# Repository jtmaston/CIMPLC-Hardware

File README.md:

<div style="text-align: justify">

# CIMPLC
The CIMPLC is a low-cost, open source high pin-count programmable logic controller, designed as a project while studying at the University of Politehnica, Bucharest. It is designed as a replacement for the aging hardware found inside the CIM ( Computer Integrated Manufacturing ) located in our faculty.

# The hardware
The CIMPLC is based, as much as possible, on readily-available parts. Since the hardware development time had to be reduced as much as possible, it was decided to simplify the control hardware, by using an ESP32 Devkit v4 at the core. Beyond that, the goal was to employ as many interfaces as possible compatible to the CIM.

## Features

### Interfaces
- RS232
- RS485
- ~~CAN~~ (See limitations)
- WiFi / Bluetooth

### Input / Output
- 12 Inputs
- 32 Outputs

### Program memory
- 125KB of EEPROM for user program storage
- 4MB of external SRAM, used for instruction caching

### Programmability
- Over the air (OTA) firmware updates
- Built-in optimizing compiler to translate IEC 61131-3 instructions to bytecode which can be loaded faster from EEPROM.
## Limitations

- Due to the fast development cycle and my inexperience with electronics, the outputs are only able to source current, not sink. The implementation, using solid-state relays, allow to source +12v when the pin is driven high, but otherwise leaves the pin floating.

- Similarly, due to my inexperience, I avoided implementing onboard power management, relying on an external +12v power supply, able to drive the pin outputs, as well as a +5v rail to power the control side. There will probably be more things , but this is all I've discovered up at this point.

- An oversight has been the fact that strapping pins 0 and 2 have been used, which control going into the bootloader. As such, all reboots would necessitate the CANH line being high.
As such, it has been removed and functionality abandoned.

## License

This project is licensed under the [CERN OHL v2 Weakly Reciprocal](https://choosealicense.com/licenses/cern-ohl-w-2.0/).

</div>

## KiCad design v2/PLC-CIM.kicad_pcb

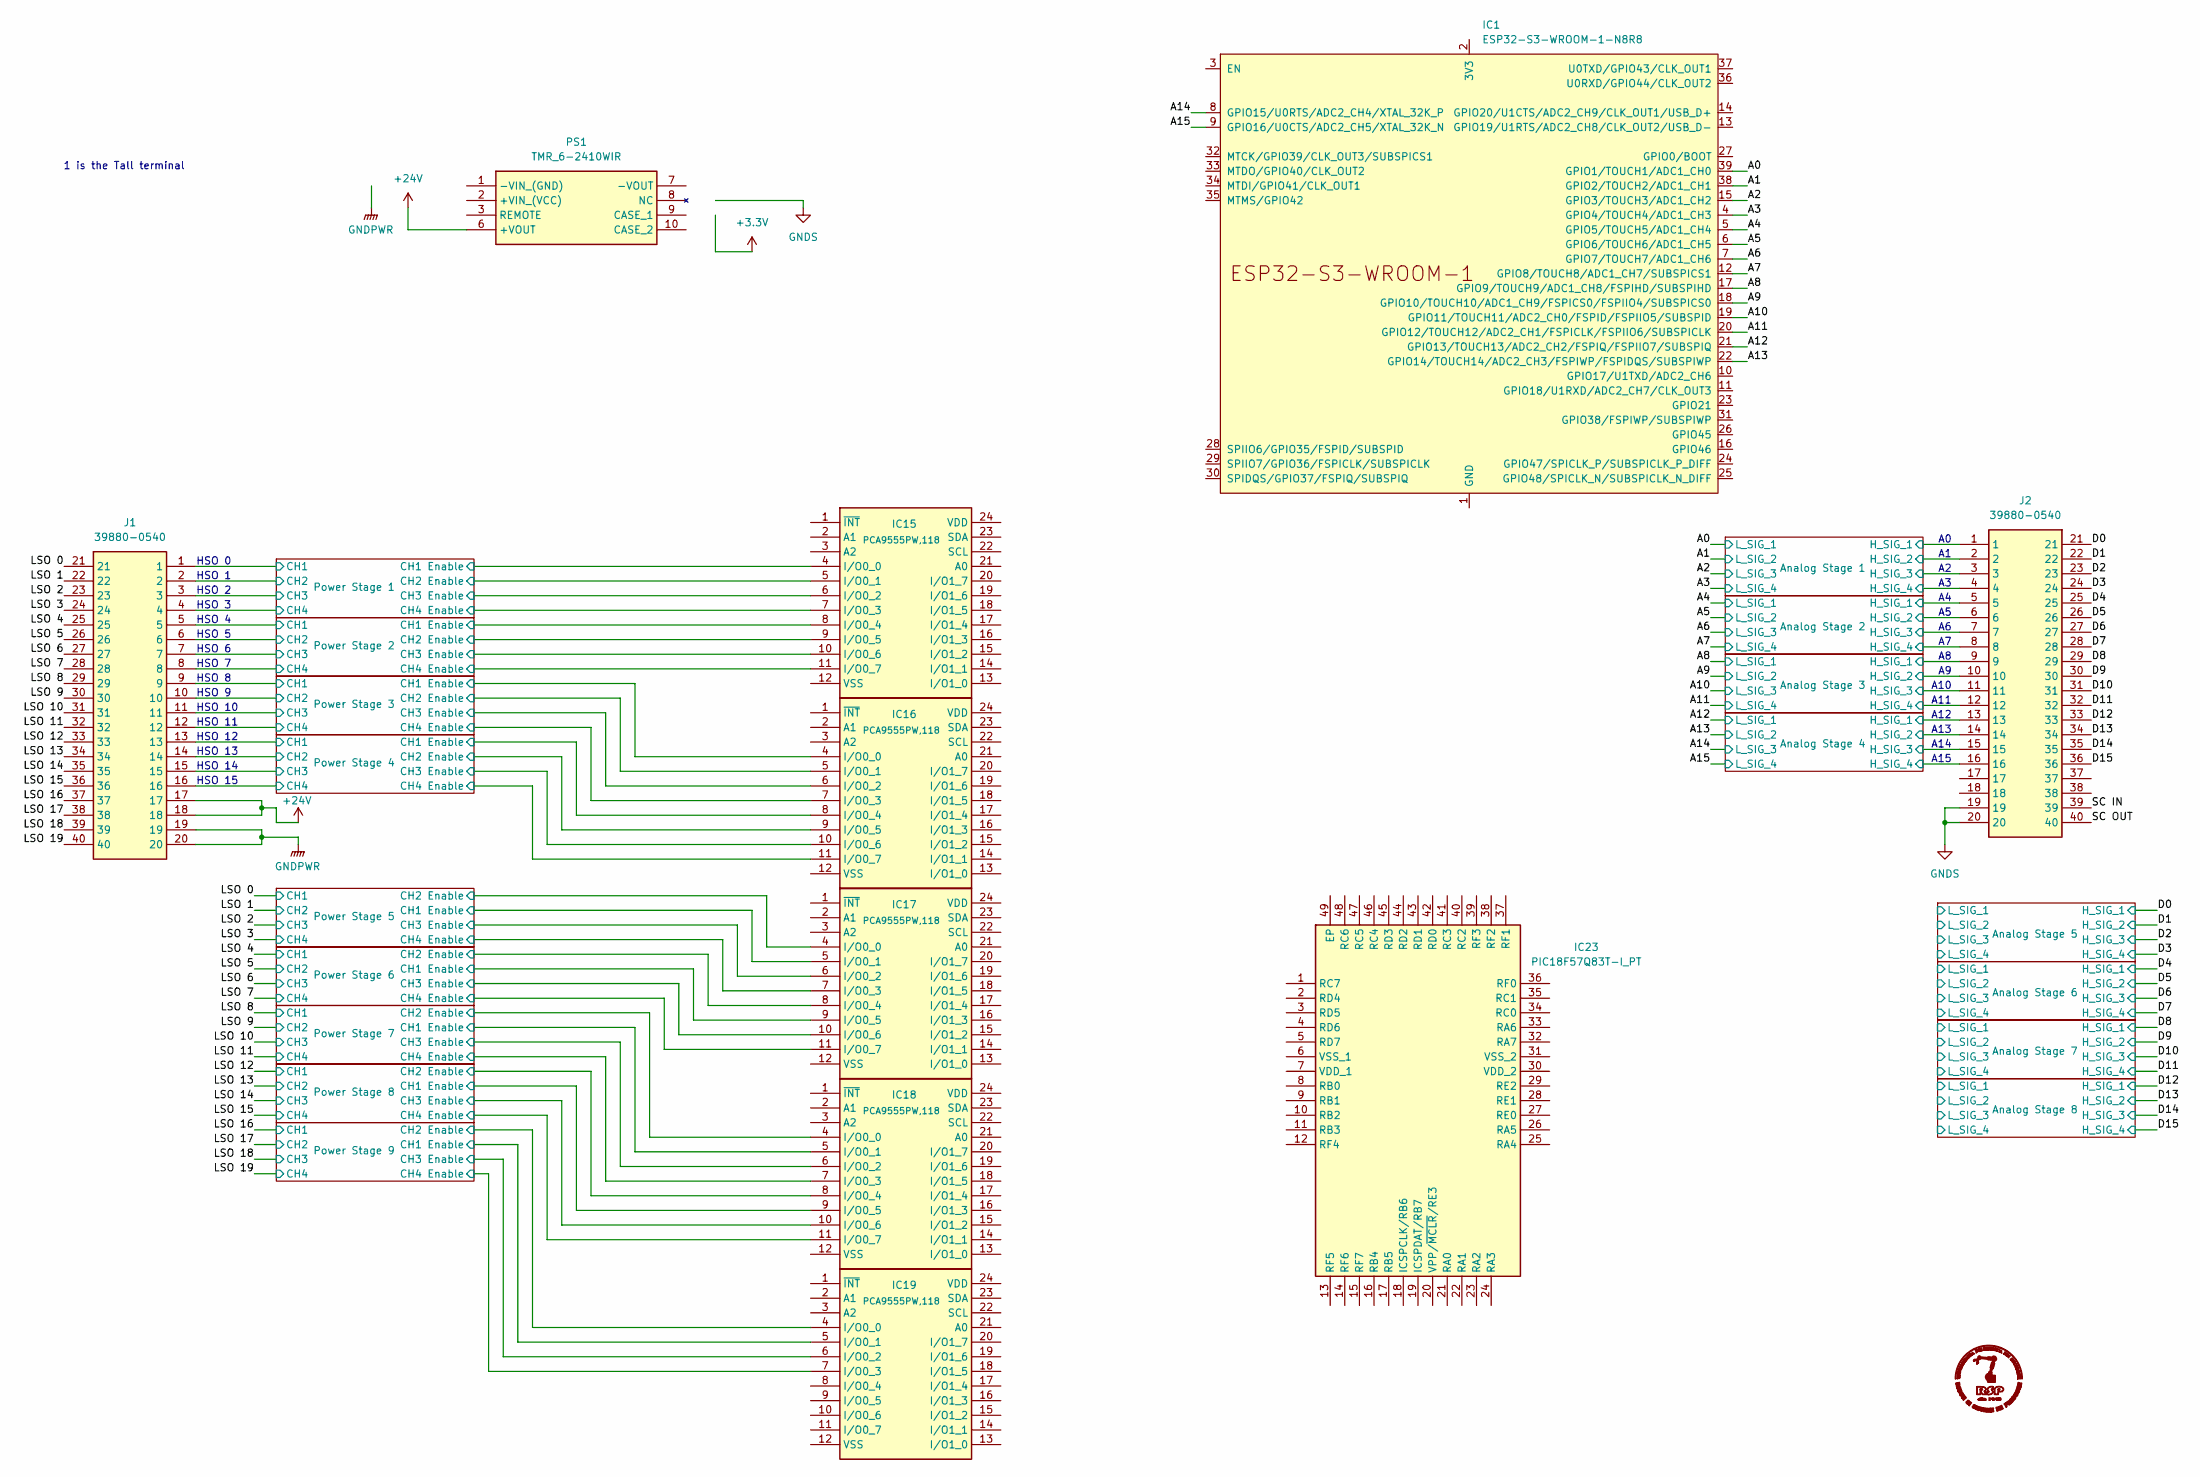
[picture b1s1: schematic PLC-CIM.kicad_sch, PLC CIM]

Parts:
IC1: ESP32-S3-WROOM-1-N8R8; ESP32S3WROOM1N8R8; Mouser Part Number 356-EP32S3WROOM1N8R8
IC15, IC16, IC17, IC18, IC19: PCA9555PW,118; SOP65P640X110-24N; Mouser Part Number 771-PCA9555PW-T
IC23: PIC18F57Q83T-I_PT; QFP50P900X900X120-49N; Mouser Part Number N/A
J1, J2: 39880-0540; 398800540; Mouser Part Number 538-39880-0540
PS1: TMR_6-2410WIR; TMR62410WIR; Mouser Part Number 495-TMR6-2410WIR

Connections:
+24V: J1.17, J1.18, PS1.6 (+VOUT); also elsewhere on the board
/A0: IC1.39 (GPIO1/TOUCH1/ADC1_CH0); also elsewhere on the board
/A1: IC1.38 (GPIO2/TOUCH2/ADC1_CH1); also elsewhere on the board
/A2: IC1.15 (GPIO3/TOUCH3/ADC1_CH2); also elsewhere on the board
/A3: IC1.4 (GPIO4/TOUCH4/ADC1_CH3); also elsewhere on the board
/A4: IC1.5 (GPIO5/TOUCH5/ADC1_CH4); also elsewhere on the board
/A5: IC1.6 (GPIO6/TOUCH6/ADC1_CH5); also elsewhere on the board
/A6: IC1.7 (GPIO7/TOUCH7/ADC1_CH6); also elsewhere on the board
/A7: IC1.12 (GPIO8/TOUCH8/ADC1_CH7/SUBSPICS1); also elsewhere on the board
/A8: IC1.17 (GPIO9/TOUCH9/ADC1_CH8/FSPIHD/SUBSPIHD); also elsewhere on the board
/A9: IC1.18 (GPIO10/TOUCH10/ADC1_CH9/FSPICS0/FSPIIO4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); also elsewhere on the board
/A10: IC1.19 (GPIO11/TOUCH11/ADC2_CH0/FSPID/FSPIIO5/S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); also elsewhere on the board
/A11: IC1.20 (GPIO12/TOUCH12/ADC2_CH1/FSPICLK/FSPIIO6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); also elsewhere on the board
/A12: IC1.21 (GPIO13/TOUCH13/ADC2_CH2/FSPIQ/FSPIIO7/S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); also elsewhere on the board
/A13: IC1.22 (GPIO14/TOUCH14/ADC2_CH3/FSPIWP/FSPIDQS/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); also elsewhere on the board
/A14: IC1.8 (GPIO15/U0RTS/ADC2_CH4/XTAL_32K_P); also elsewhere on the board
/A15: IC1.9 (GPIO16/U0CTS/ADC2_CH5/XTAL_32K_N); also elsewhere on the board
/Analog Stage 1/H_SIG_1: J2.1; also elsewhere on the board
/Analog Stage 1/H_SIG_2: J2.2; also elsewhere on the board
/Analog Stage 1/H_SIG_3: J2.3; also elsewhere on the board
/Analog Stage 1/H_SIG_4: J2.4; also elsewhere on the board
/Analog Stage 2/H_SIG_1: J2.5; also elsewhere on the board
/Analog Stage 2/H_SIG_2: J2.6; also elsewhere on the board
/Analog Stage 2/H_SIG_3: J2.7; also elsewhere on the board
/Analog Stage 2/H_SIG_4: J2.8; also elsewhere on the board
/Analog Stage 3/H_SIG_1: J2.9; also elsewhere on the board
/Analog Stage 3/H_SIG_2: J2.10; also elsewhere on the board
/Analog Stage 3/H_SIG_3: J2.11; also elsewhere on the board
/Analog Stage 3/H_SIG_4: J2.12; also elsewhere on the board
/Analog Stage 4/H_SIG_1: J2.13; also elsewhere on the board
/Analog Stage 4/H_SIG_2: J2.14; also elsewhere on the board
/Analog Stage 4/H_SIG_3: J2.15; also elsewhere on the board
/Analog Stage 4/H_SIG_4: J2.16; also elsewhere on the board
/D0: J2.21; also elsewhere on the board
/D1: J2.22; also elsewhere on the board
/D2: J2.23; also elsewhere on the board
/D3: J2.24; also elsewhere on the board
/D4: J2.25; also elsewhere on the board
/D5: J2.26; also elsewhere on the board
/D6: J2.27; also elsewhere on the board
/D7: J2.28; also elsewhere on the board
/D8: J2.29; also elsewhere on the board
/D9: J2.30; also elsewhere on the board
/D10: J2.31; also elsewhere on the board
/D11: J2.32; also elsewhere on the board
/D12: J2.33; also elsewhere on the board
/D13: J2.34; also elsewhere on the board
/D14: J2.35; also elsewhere on the board
/D15: J2.36; also elsewhere on the board
/LSO 0: J1.21; also elsewhere on the board
/LSO 1: J1.22; also elsewhere on the board
/LSO 2: J1.23; also elsewhere on the board
/LSO 3: J1.24; also elsewhere on the board
/LSO 4: J1.25; also elsewhere on the board
/LSO 5: J1.26; also elsewhere on the board
/LSO 6: J1.27; also elsewhere on the board
/LSO 7: J1.28; also elsewhere on the board
/LSO 8: J1.29; also elsewhere on the board
/LSO 9: J1.30; also elsewhere on the board
/LSO 10: J1.31; also elsewhere on the board
/LSO 11: J1.32; also elsewhere on the board
/LSO 12: J1.33; also elsewhere on the board
/LSO 13: J1.34; also elsewhere on the board
/LSO 14: J1.35; also elsewhere on the board
/LSO 15: J1.36; also elsewhere on the board
/LSO 16: J1.37; also elsewhere on the board
/LSO 17: J1.38; also elsewhere on the board
/LSO 18: J1.39; also elsewhere on the board
/LSO 19: J1.40; also elsewhere on the board
/Power Stage 1/CH1: J1.1; also elsewhere on the board
/Power Stage 1/CH1 Enable: IC15.4 (I/O0_0); also elsewhere on the board
/Power Stage 1/CH2: J1.2; also elsewhere on the board
/Power Stage 1/CH2 Enable: IC15.5 (I/O0_1); also elsewhere on the board
/Power Stage 1/CH3: J1.3; also elsewhere on the board
/Power Stage 1/CH3 Enable: IC15.6 (I/O0_2); also elsewhere on the board
/Power Stage 1/CH4: J1.4; also elsewhere on the board
/Power Stage 1/CH4 Enable: IC15.7 (I/O0_3); also elsewhere on the board
/Power Stage 2/CH1: J1.5; also elsewhere on the board
/Power Stage 2/CH1 Enable: IC15.8 (I/O0_4); also elsewhere on the board
/Power Stage 2/CH2: J1.6; also elsewhere on the board
/Power Stage 2/CH2 Enable: IC15.9 (I/O0_5); also elsewhere on the board
/Power Stage 2/CH3: J1.7; also elsewhere on the board
/Power Stage 2/CH3 Enable: IC15.10 (I/O0_6); also elsewhere on the board
/Power Stage 2/CH4: J1.8; also elsewhere on the board
/Power Stage 2/CH4 Enable: IC15.11 (I/O0_7); also elsewhere on the board
/Power Stage 3/CH1: J1.9; also elsewhere on the board
/Power Stage 3/CH1 Enable: IC16.4 (I/O0_0); also elsewhere on the board
/Power Stage 3/CH2: J1.10; also elsewhere on the board
/Power Stage 3/CH2 Enable: IC16.5 (I/O0_1); also elsewhere on the board
/Power Stage 3/CH3: J1.11; also elsewhere on the board
/Power Stage 3/CH3 Enable: IC16.6 (I/O0_2); also elsewhere on the board
/Power Stage 3/CH4: J1.12; also elsewhere on the board
/Power Stage 3/CH4 Enable: IC16.7 (I/O0_3); also elsewhere on the board
/Power Stage 4/CH1: J1.13; also elsewhere on the board
/Power Stage 4/CH1 Enable: IC16.8 (I/O0_4); also elsewhere on the board
/Power Stage 4/CH2: J1.14; also elsewhere on the board
/Power Stage 4/CH2 Enable: IC16.9 (I/O0_5); also elsewhere on the board
/Power Stage 4/CH3: J1.15; also elsewhere on the board
/Power Stage 4/CH3 Enable: IC16.10 (I/O0_6); also elsewhere on the board
/Power Stage 4/CH4: J1.16; also elsewhere on the board
/Power Stage 4/CH4 Enable: IC16.11 (I/O0_7); also elsewhere on the board
/Power Stage 5/CH1 Enable: IC17.5 (I/O0_1); also elsewhere on the board
/Power Stage 5/CH2 Enable: IC17.4 (I/O0_0); also elsewhere on the board
/Power Stage 5/CH3 Enable: IC17.6 (I/O0_2); also elsewhere on the board
/Power Stage 5/CH4 Enable: IC17.7 (I/O0_3); also elsewhere on the board
/Power Stage 6/CH1 Enable: IC17.9 (I/O0_5); also elsewhere on the board
/Power Stage 6/CH2 Enable: IC17.8 (I/O0_4); also elsewhere on the board
/Power Stage 6/CH3 Enable: IC17.10 (I/O0_6); also elsewhere on the board
/Power Stage 6/CH4 Enable: IC17.11 (I/O0_7); also elsewhere on the board
/Power Stage 7/CH1 Enable: IC18.5 (I/O0_1); also elsewhere on the board
/Power Stage 7/CH2 Enable: IC18.4 (I/O0_0); also elsewhere on the board
/Power Stage 7/CH3 Enable: IC18.6 (I/O0_2); also elsewhere on the board
/Power Stage 7/CH4 Enable: IC18.7 (I/O0_3); also elsewhere on the board
/Power Stage 8/CH1 Enable: IC18.9 (I/O0_5); also elsewhere on the board
/Power Stage 8/CH2 Enable: IC18.8 (I/O0_4); also elsewhere on the board
/Power Stage 8/CH3 Enable: IC18.10 (I/O0_6); also elsewhere on the board
/Power Stage 8/CH4 Enable: IC18.11 (I/O0_7); also elsewhere on the board
/Power Stage 9/CH1 Enable: IC19.5 (I/O0_1); also elsewhere on the board
/Power Stage 9/CH2 Enable: IC19.4 (I/O0_0); also elsewhere on the board
/Power Stage 9/CH3 Enable: IC19.6 (I/O0_2); also elsewhere on the board
/Power Stage 9/CH4 Enable: IC19.7 (I/O0_3); also elsewhere on the board
/SC IN: J2.39
/SC OUT: J2.40
GNDPWR: J1.19, J1.20; also elsewhere on the board
GNDS: J2.19, J2.20; also elsewhere on the board
unnamed: IC1.1 (GND), IC1.40 (GND), IC1.41 (GND)

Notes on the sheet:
HSO 4
HSO 11
HSO 0
A12
HSO 10
HSO 15
HSO 12
A14
1 is the Tall terminal
HSO 13
HSO 5
HSO 14
HSO 3
A13
HSO 9
HSO 2
HSO 1
HSO 8
HSO 6
A10
HSO 7
A11
A15

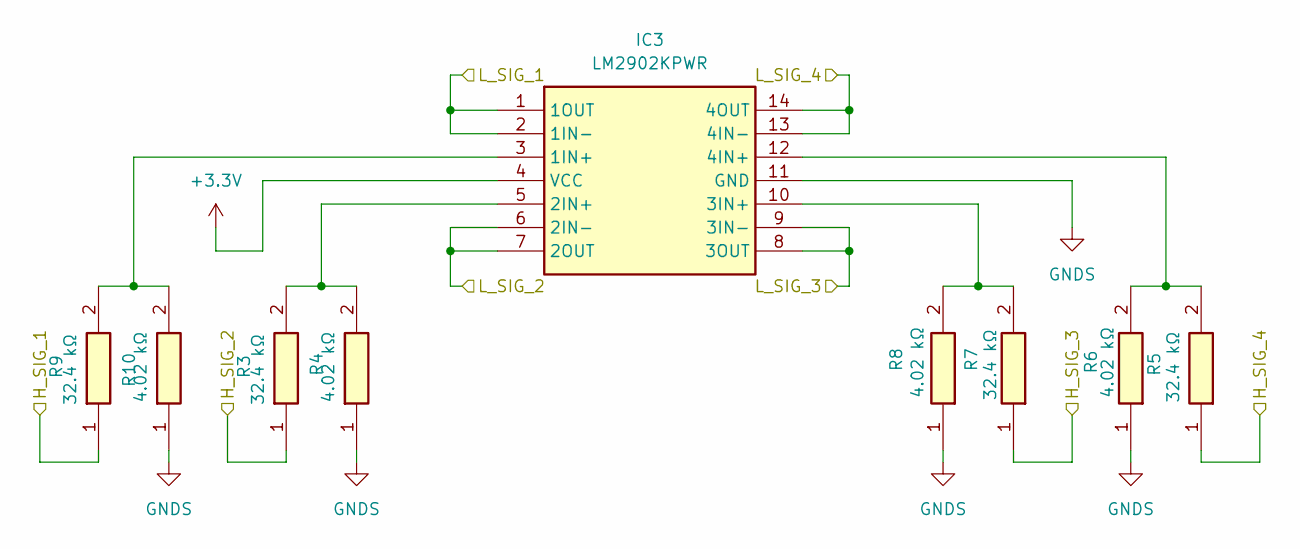
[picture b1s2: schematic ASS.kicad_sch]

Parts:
IC3: LM2902KPWR; SOP65P640X120-14N; Mouser Part Number 595-LM2902KPWR
R3, R5, R7, R9: 32.4 kΩ; RESC1609X55N; Mouser Part Number 667-ERJ-P03F3242V
R4, R6, R8, R10: 4.02 kΩ; RESC1609X55N; Mouser Part Number 71-CRCW12064K02FKEAH

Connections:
+3.3V: IC3.4 (VCC); also elsewhere on the board
/A4: IC3.1 (1OUT), IC3.2 (1IN-); also elsewhere on the board
/A5: IC3.6 (2IN-), IC3.7 (2OUT); also elsewhere on the board
/A6: IC3.8 (3OUT), IC3.9 (3IN-); also elsewhere on the board
/A7: IC3.13 (4IN-), IC3.14 (4OUT); also elsewhere on the board
/Analog Stage 1/H_SIG_2: R3.1; also elsewhere on the board
/Analog Stage 1/H_SIG_3: R7.1; also elsewhere on the board
/Analog Stage 1/H_SIG_4: R5.1; also elsewhere on the board
/Analog Stage 2/H_SIG_1: R9.1; also elsewhere on the board
GNDS: IC3.11 (GND), R4.1, R6.1, R8.1, R10.1; also elsewhere on the board
unnamed: IC3.3 (1IN+), R9.2, R10.2

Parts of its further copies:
IC2, IC4, IC5, IC20, IC21, IC22, IC24: LM2902KPWR; SOP65P640X120-14N; Mouser Part Number 595-LM2902KPWR
R1, R11, R14, R16, R17, R19, R22, R24, R25, R27, R30, R32, R33, R35, R38, R40, R41, R44, R46, R47, R49, R52, R54, R55, R57, R60, R62, R63: 32.4 kΩ; RESC1609X55N; Mouser Part Number 667-ERJ-P03F3242V
R2, R12, R13, R15, R18, R20, R21, R23, R26, R28, R29, R31, R34, R36, R37, R39, R42, R43, R45, R48, R50, R51, R53, R56, R58, R59, R61, R64: 4.02 kΩ; RESC1609X55N; Mouser Part Number 71-CRCW12064K02FKEAH

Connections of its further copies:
+3.3V: IC2.4 (VCC), IC4.4 (VCC), IC5.4 (VCC), IC20.4 (VCC), IC21.4 (VCC), IC22.4 (VCC), IC24.4 (VCC); also elsewhere on the board
/A0: IC24.1 (1OUT), IC24.2 (1IN-); also elsewhere on the board
/A1: IC24.6 (2IN-), IC24.7 (2OUT); also elsewhere on the board
/A2: IC24.8 (3OUT), IC24.9 (3IN-); also elsewhere on the board
/A3: IC24.13 (4IN-), IC24.14 (4OUT); also elsewhere on the board
/A8: IC4.1 (1OUT), IC4.2 (1IN-); also elsewhere on the board
/A9: IC4.6 (2IN-), IC4.7 (2OUT); also elsewhere on the board
/A10: IC4.8 (3OUT), IC4.9 (3IN-); also elsewhere on the board
/A11: IC4.13 (4IN-), IC4.14 (4OUT); also elsewhere on the board
/A12: IC5.1 (1OUT), IC5.2 (1IN-); also elsewhere on the board
/A13: IC5.6 (2IN-), IC5.7 (2OUT); also elsewhere on the board
/A14: IC5.8 (3OUT), IC5.9 (3IN-); also elsewhere on the board
/A15: IC5.13 (4IN-), IC5.14 (4OUT); also elsewhere on the board
/Analog Stage 1/H_SIG_1: R25.1; also elsewhere on the board
/Analog Stage 2/H_SIG_2: R11.1; also elsewhere on the board
/Analog Stage 2/H_SIG_3: R14.1; also elsewhere on the board
/Analog Stage 2/H_SIG_4: R16.1; also elsewhere on the board
/Analog Stage 3/H_SIG_1: R17.1; also elsewhere on the board
/Analog Stage 3/H_SIG_2: R19.1; also elsewhere on the board
/Analog Stage 3/H_SIG_3: R22.1; also elsewhere on the board
/Analog Stage 3/H_SIG_4: R24.1; also elsewhere on the board
/Analog Stage 4/H_SIG_1: R63.1; also elsewhere on the board
/Analog Stage 4/H_SIG_2: R27.1; also elsewhere on the board
/Analog Stage 4/H_SIG_3: R30.1; also elsewhere on the board
/Analog Stage 4/H_SIG_4: R32.1; also elsewhere on the board
/Analog Stage 5/L_SIG_1: IC20.1 (1OUT), IC20.2 (1IN-)
/Analog Stage 5/L_SIG_2: IC20.6 (2IN-), IC20.7 (2OUT)
/Analog Stage 5/L_SIG_3: IC20.8 (3OUT), IC20.9 (3IN-)
/Analog Stage 5/L_SIG_4: IC20.13 (4IN-), IC20.14 (4OUT)
/Analog Stage 6/L_SIG_1: IC2.1 (1OUT), IC2.2 (1IN-)
/Analog Stage 6/L_SIG_2: IC2.6 (2IN-), IC2.7 (2OUT)
/Analog Stage 6/L_SIG_3: IC2.8 (3OUT), IC2.9 (3IN-)
/Analog Stage 6/L_SIG_4: IC2.13 (4IN-), IC2.14 (4OUT)
/Analog Stage 7/L_SIG_1: IC21.1 (1OUT), IC21.2 (1IN-)
/Analog Stage 7/L_SIG_2: IC21.6 (2IN-), IC21.7 (2OUT)
/Analog Stage 7/L_SIG_3: IC21.8 (3OUT), IC21.9 (3IN-)
/Analog Stage 7/L_SIG_4: IC21.13 (4IN-), IC21.14 (4OUT)
/Analog Stage 8/L_SIG_1: IC22.1 (1OUT), IC22.2 (1IN-)
/Analog Stage 8/L_SIG_2: IC22.6 (2IN-), IC22.7 (2OUT)
/Analog Stage 8/L_SIG_3: IC22.8 (3OUT), IC22.9 (3IN-)
/Analog Stage 8/L_SIG_4: IC22.13 (4IN-), IC22.14 (4OUT)
/D0: R33.1; also elsewhere on the board
/D1: R35.1; also elsewhere on the board
/D2: R38.1; also elsewhere on the board
/D3: R40.1; also elsewhere on the board
/D4: R1.1; also elsewhere on the board
/D5: R41.1; also elsewhere on the board
/D6: R44.1; also elsewhere on the board
/D7: R46.1; also elsewhere on the board
/D8: R47.1; also elsewhere on the board
/D9: R49.1; also elsewhere on the board
/D10: R52.1; also elsewhere on the board
/D11: R54.1; also elsewhere on the board
/D12: R55.1; also elsewhere on the board
/D13: R57.1; also elsewhere on the board
/D14: R60.1; also elsewhere on the board
/D15: R62.1; also elsewhere on the board
GNDS: IC2.11 (GND), IC4.11 (GND), IC5.11 (GND), IC20.11 (GND), IC21.11 (GND), IC22.11 (GND), IC24.11 (GND), R2.1, R12.1, R13.1, R15.1, R18.1, R20.1, R21.1, R23.1, R26.1, R28.1, R29.1, R31.1, R34.1, R36.1, R37.1, R39.1, R42.1, R43.1, R45.1, R48.1, R50.1, R51.1, R53.1, R56.1, R58.1, R59.1, R61.1, R64.1; also elsewhere on the board
unnamed: IC2.3 (1IN+), R1.2, R2.2
unnamed: IC2.5 (2IN+), R41.2, R42.2
unnamed: IC2.10 (3IN+), R43.2, R44.2
unnamed: IC2.12 (4IN+), R45.2, R46.2
unnamed: IC4.3 (1IN+), R17.2, R18.2
unnamed: IC4.5 (2IN+), R19.2, R20.2
unnamed: IC4.10 (3IN+), R21.2, R22.2
unnamed: IC4.12 (4IN+), R23.2, R24.2
unnamed: IC5.3 (1IN+), R63.2, R64.2
unnamed: IC5.5 (2IN+), R27.2, R28.2
unnamed: IC5.10 (3IN+), R29.2, R30.2
unnamed: IC5.12 (4IN+), R31.2, R32.2
unnamed: IC20.3 (1IN+), R33.2, R34.2
unnamed: IC20.5 (2IN+), R35.2, R36.2
unnamed: IC20.10 (3IN+), R37.2, R38.2
unnamed: IC20.12 (4IN+), R39.2, R40.2
unnamed: IC21.3 (1IN+), R47.2, R48.2
unnamed: IC21.5 (2IN+), R49.2, R50.2
unnamed: IC21.10 (3IN+), R51.2, R52.2
unnamed: IC21.12 (4IN+), R53.2, R54.2
unnamed: IC22.3 (1IN+), R55.2, R56.2
unnamed: IC22.5 (2IN+), R57.2, R58.2
unnamed: IC22.10 (3IN+), R59.2, R60.2
unnamed: IC22.12 (4IN+), R61.2, R62.2
unnamed: IC24.3 (1IN+), R25.2, R26.2

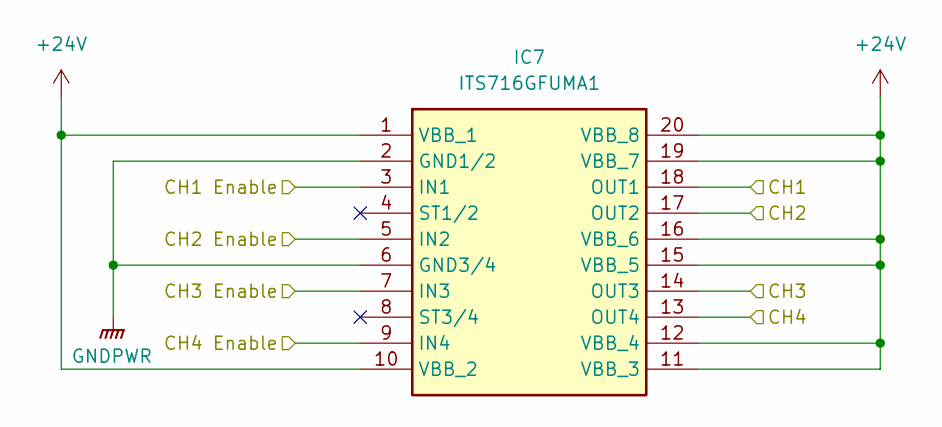
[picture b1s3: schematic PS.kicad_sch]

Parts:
IC7: ITS716GFUMA1; SOIC127P1030X265-20N; Mouser Part Number 726-ITS716GFUMA1

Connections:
+24V: IC7.1 (VBB_1), IC7.10 (VBB_2), IC7.11 (VBB_3), IC7.12 (VBB_4), IC7.15 (VBB_5), IC7.16 (VBB_6), IC7.19 (VBB_7), IC7.20 (VBB_8); also elsewhere on the board
/Power Stage 2/CH1: IC7.18 (OUT1); also elsewhere on the board
/Power Stage 2/CH1 Enable: IC7.3 (IN1); also elsewhere on the board
/Power Stage 2/CH2: IC7.17 (OUT2); also elsewhere on the board
/Power Stage 2/CH2 Enable: IC7.5 (IN2); also elsewhere on the board
/Power Stage 2/CH3: IC7.14 (OUT3); also elsewhere on the board
/Power Stage 2/CH3 Enable: IC7.7 (IN3); also elsewhere on the board
/Power Stage 2/CH4: IC7.13 (OUT4); also elsewhere on the board
/Power Stage 2/CH4 Enable: IC7.9 (IN4); also elsewhere on the board
GNDPWR: IC7.2 (GND1/2), IC7.6 (GND3/4); also elsewhere on the board

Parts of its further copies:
IC6, IC8, IC9, IC10, IC11, IC12, IC13, IC14: ITS716GFUMA1; SOIC127P1030X265-20N; Mouser Part Number 726-ITS716GFUMA1

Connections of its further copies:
+24V: IC6.1 (VBB_1), IC6.10 (VBB_2), IC6.11 (VBB_3), IC6.12 (VBB_4), IC6.15 (VBB_5), IC6.16 (VBB_6), IC6.19 (VBB_7), IC6.20 (VBB_8), IC8.1 (VBB_1), IC8.10 (VBB_2), IC8.11 (VBB_3), IC8.12 (VBB_4), IC8.15 (VBB_5), IC8.16 (VBB_6), IC8.19 (VBB_7), IC8.20 (VBB_8), IC9.1 (VBB_1), IC9.10 (VBB_2), IC9.11 (VBB_3), IC9.12 (VBB_4), IC9.15 (VBB_5), IC9.16 (VBB_6), IC9.19 (VBB_7), IC9.20 (VBB_8), IC10.1 (VBB_1), IC10.10 (VBB_2), IC10.11 (VBB_3), IC10.12 (VBB_4), IC10.15 (VBB_5), IC10.16 (VBB_6), IC10.19 (VBB_7), IC10.20 (VBB_8), IC11.1 (VBB_1), IC11.10 (VBB_2), IC11.11 (VBB_3), IC11.12 (VBB_4), IC11.15 (VBB_5), IC11.16 (VBB_6), IC11.19 (VBB_7), IC11.20 (VBB_8), IC12.1 (VBB_1), IC12.10 (VBB_2), IC12.11 (VBB_3), IC12.12 (VBB_4), IC12.15 (VBB_5), IC12.16 (VBB_6), IC12.19 (VBB_7), IC12.20 (VBB_8), IC13.1 (VBB_1), IC13.10 (VBB_2), IC13.11 (VBB_3), IC13.12 (VBB_4), IC13.15 (VBB_5), IC13.16 (VBB_6), IC13.19 (VBB_7), IC13.20 (VBB_8), IC14.1 (VBB_1), IC14.10 (VBB_2), IC14.11 (VBB_3), IC14.12 (VBB_4), IC14.15 (VBB_5), IC14.16 (VBB_6), IC14.19 (VBB_7), IC14.20 (VBB_8); also elsewhere on the board
/LSO 0: IC10.18 (OUT1); also elsewhere on the board
/LSO 1: IC10.17 (OUT2); also elsewhere on the board
/LSO 2: IC10.14 (OUT3); also elsewhere on the board
/LSO 3: IC10.13 (OUT4); also elsewhere on the board
/LSO 4: IC11.18 (OUT1); also elsewhere on the board
/LSO 5: IC11.17 (OUT2); also elsewhere on the board
/LSO 6: IC11.14 (OUT3); also elsewhere on the board
/LSO 7: IC11.13 (OUT4); also elsewhere on the board
/LSO 8: IC12.18 (OUT1); also elsewhere on the board
/LSO 9: IC12.17 (OUT2); also elsewhere on the board
/LSO 10: IC12.14 (OUT3); also elsewhere on the board
/LSO 11: IC12.13 (OUT4); also elsewhere on the board
/LSO 12: IC13.18 (OUT1); also elsewhere on the board
/LSO 13: IC13.17 (OUT2); also elsewhere on the board
/LSO 14: IC13.14 (OUT3); also elsewhere on the board
/LSO 15: IC13.13 (OUT4); also elsewhere on the board
/LSO 16: IC14.18 (OUT1); also elsewhere on the board
/LSO 17: IC14.17 (OUT2); also elsewhere on the board
/LSO 18: IC14.14 (OUT3); also elsewhere on the board
/LSO 19: IC14.13 (OUT4); also elsewhere on the board
/Power Stage 1/CH1: IC6.18 (OUT1); also elsewhere on the board
/Power Stage 1/CH1 Enable: IC6.3 (IN1); also elsewhere on the board
/Power Stage 1/CH2: IC6.17 (OUT2); also elsewhere on the board
/Power Stage 1/CH2 Enable: IC6.5 (IN2); also elsewhere on the board
/Power Stage 1/CH3: IC6.14 (OUT3); also elsewhere on the board
/Power Stage 1/CH3 Enable: IC6.7 (IN3); also elsewhere on the board
/Power Stage 1/CH4: IC6.13 (OUT4); also elsewhere on the board
/Power Stage 1/CH4 Enable: IC6.9 (IN4); also elsewhere on the board
/Power Stage 3/CH1: IC8.18 (OUT1); also elsewhere on the board
/Power Stage 3/CH1 Enable: IC8.3 (IN1); also elsewhere on the board
/Power Stage 3/CH2: IC8.17 (OUT2); also elsewhere on the board
/Power Stage 3/CH2 Enable: IC8.5 (IN2); also elsewhere on the board
/Power Stage 3/CH3: IC8.14 (OUT3); also elsewhere on the board
/Power Stage 3/CH3 Enable: IC8.7 (IN3); also elsewhere on the board
/Power Stage 3/CH4: IC8.13 (OUT4); also elsewhere on the board
/Power Stage 3/CH4 Enable: IC8.9 (IN4); also elsewhere on the board
/Power Stage 4/CH1: IC9.18 (OUT1); also elsewhere on the board
/Power Stage 4/CH1 Enable: IC9.3 (IN1); also elsewhere on the board
/Power Stage 4/CH2: IC9.17 (OUT2); also elsewhere on the board
/Power Stage 4/CH2 Enable: IC9.5 (IN2); also elsewhere on the board
/Power Stage 4/CH3: IC9.14 (OUT3); also elsewhere on the board
/Power Stage 4/CH3 Enable: IC9.7 (IN3); also elsewhere on the board
/Power Stage 4/CH4: IC9.13 (OUT4); also elsewhere on the board
/Power Stage 4/CH4 Enable: IC9.9 (IN4); also elsewhere on the board
/Power Stage 5/CH1 Enable: IC10.3 (IN1); also elsewhere on the board
/Power Stage 5/CH2 Enable: IC10.5 (IN2); also elsewhere on the board
/Power Stage 5/CH3 Enable: IC10.7 (IN3); also elsewhere on the board
/Power Stage 5/CH4 Enable: IC10.9 (IN4); also elsewhere on the board
/Power Stage 6/CH1 Enable: IC11.3 (IN1); also elsewhere on the board
/Power Stage 6/CH2 Enable: IC11.5 (IN2); also elsewhere on the board
/Power Stage 6/CH3 Enable: IC11.7 (IN3); also elsewhere on the board
/Power Stage 6/CH4 Enable: IC11.9 (IN4); also elsewhere on the board
/Power Stage 7/CH1 Enable: IC12.3 (IN1); also elsewhere on the board
/Power Stage 7/CH2 Enable: IC12.5 (IN2); also elsewhere on the board
/Power Stage 7/CH3 Enable: IC12.7 (IN3); also elsewhere on the board
/Power Stage 7/CH4 Enable: IC12.9 (IN4); also elsewhere on the board
/Power Stage 8/CH1 Enable: IC13.3 (IN1); also elsewhere on the board
/Power Stage 8/CH2 Enable: IC13.5 (IN2); also elsewhere on the board
/Power Stage 8/CH3 Enable: IC13.7 (IN3); also elsewhere on the board
/Power Stage 8/CH4 Enable: IC13.9 (IN4); also elsewhere on the board
/Power Stage 9/CH1 Enable: IC14.3 (IN1); also elsewhere on the board
/Power Stage 9/CH2 Enable: IC14.5 (IN2); also elsewhere on the board
/Power Stage 9/CH3 Enable: IC14.7 (IN3); also elsewhere on the board
/Power Stage 9/CH4 Enable: IC14.9 (IN4); also elsewhere on the board
GNDPWR: IC6.2 (GND1/2), IC6.6 (GND3/4), IC8.2 (GND1/2), IC8.6 (GND3/4), IC9.2 (GND1/2), IC9.6 (GND3/4), IC10.2 (GND1/2), IC10.6 (GND3/4), IC11.2 (GND1/2), IC11.6 (GND3/4), IC12.2 (GND1/2), IC12.6 (GND3/4), IC13.2 (GND1/2), IC13.6 (GND3/4), IC14.2 (GND1/2), IC14.6 (GND3/4); also elsewhere on the board

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
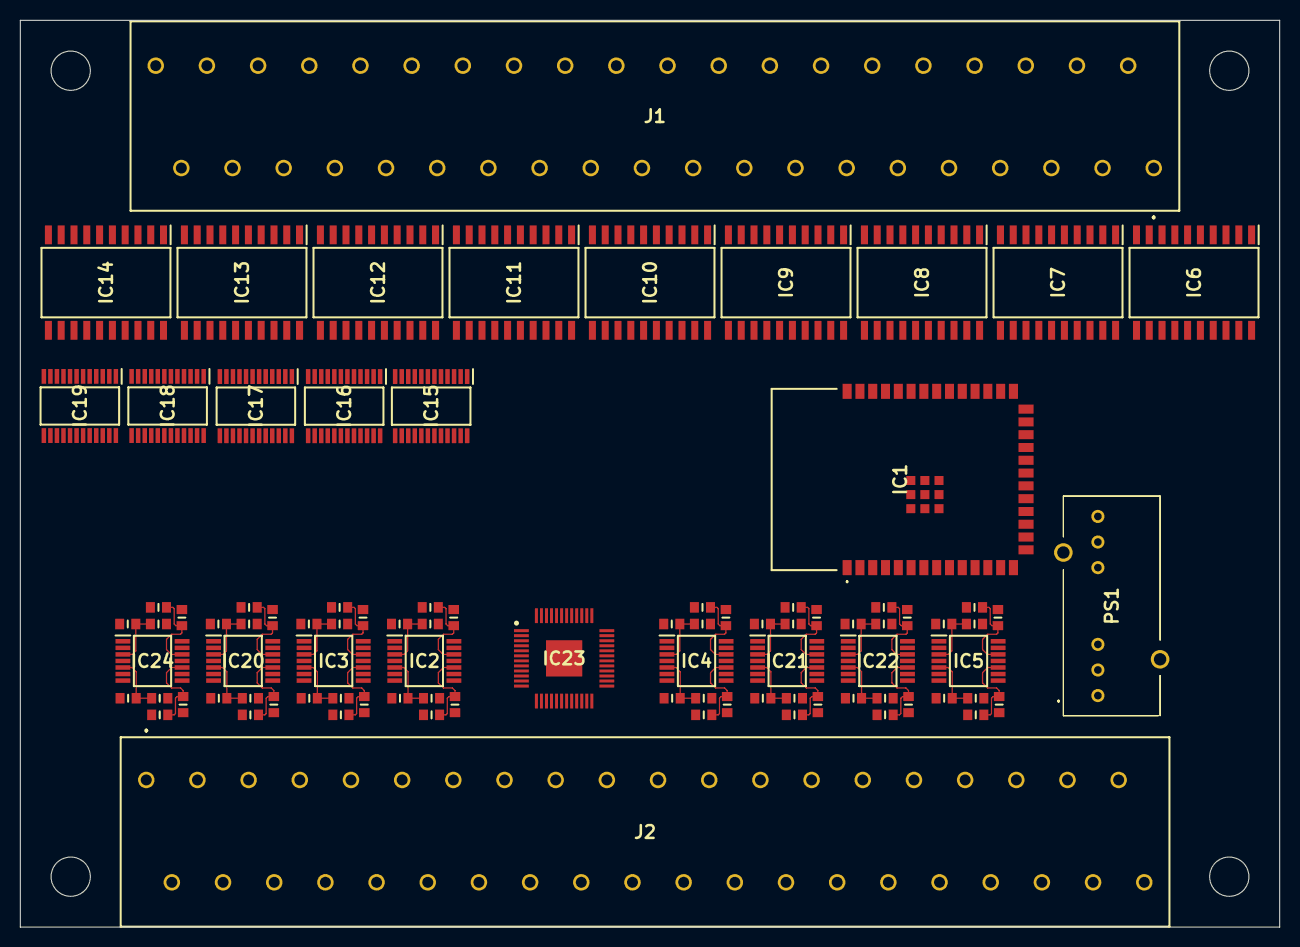
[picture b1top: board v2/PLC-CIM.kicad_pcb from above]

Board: 4 copper layers, 125.0 x 90.0 mm, 91 parts (0 on the bottom side), 173 nets.
